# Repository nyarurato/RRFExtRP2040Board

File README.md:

# RP2040 CAN IO Expansion Board
This is a CAN-connected I/O expansion board for Duet3 (RepRapFirmware) using the RP2040 and MCP2518FD.
The circuit design was heavily inspired by the [Duet3 Mainboard 6HC](https://github.com/Duet3D/Duet3-Mainboard-6HC) and the [Fly-RRF-36](https://github.com/Mellow-3D/Fly-RRF-36).

---

# RP2040 CAN IO Expansion Board
RP2040 + MCP2518FD を使用した、Duet3 (RepRapFirmware) 向けの CAN 接続 IO 拡張基板です。
回路設計は[Duet3 Mainboard 6HC](https://github.com/Duet3D/Duet3-Mainboard-6HC)と[Fly-RRF-36](https://github.com/Mellow-3D/Fly-RRF-36)を大いに参考にしました。

## v0.1

## v0.2

# firmware
以下のRP2040 & MCP2517対応のDuet3Expansionフォークを使う  
https://github.com/gloomyandy/Duet3Expansion

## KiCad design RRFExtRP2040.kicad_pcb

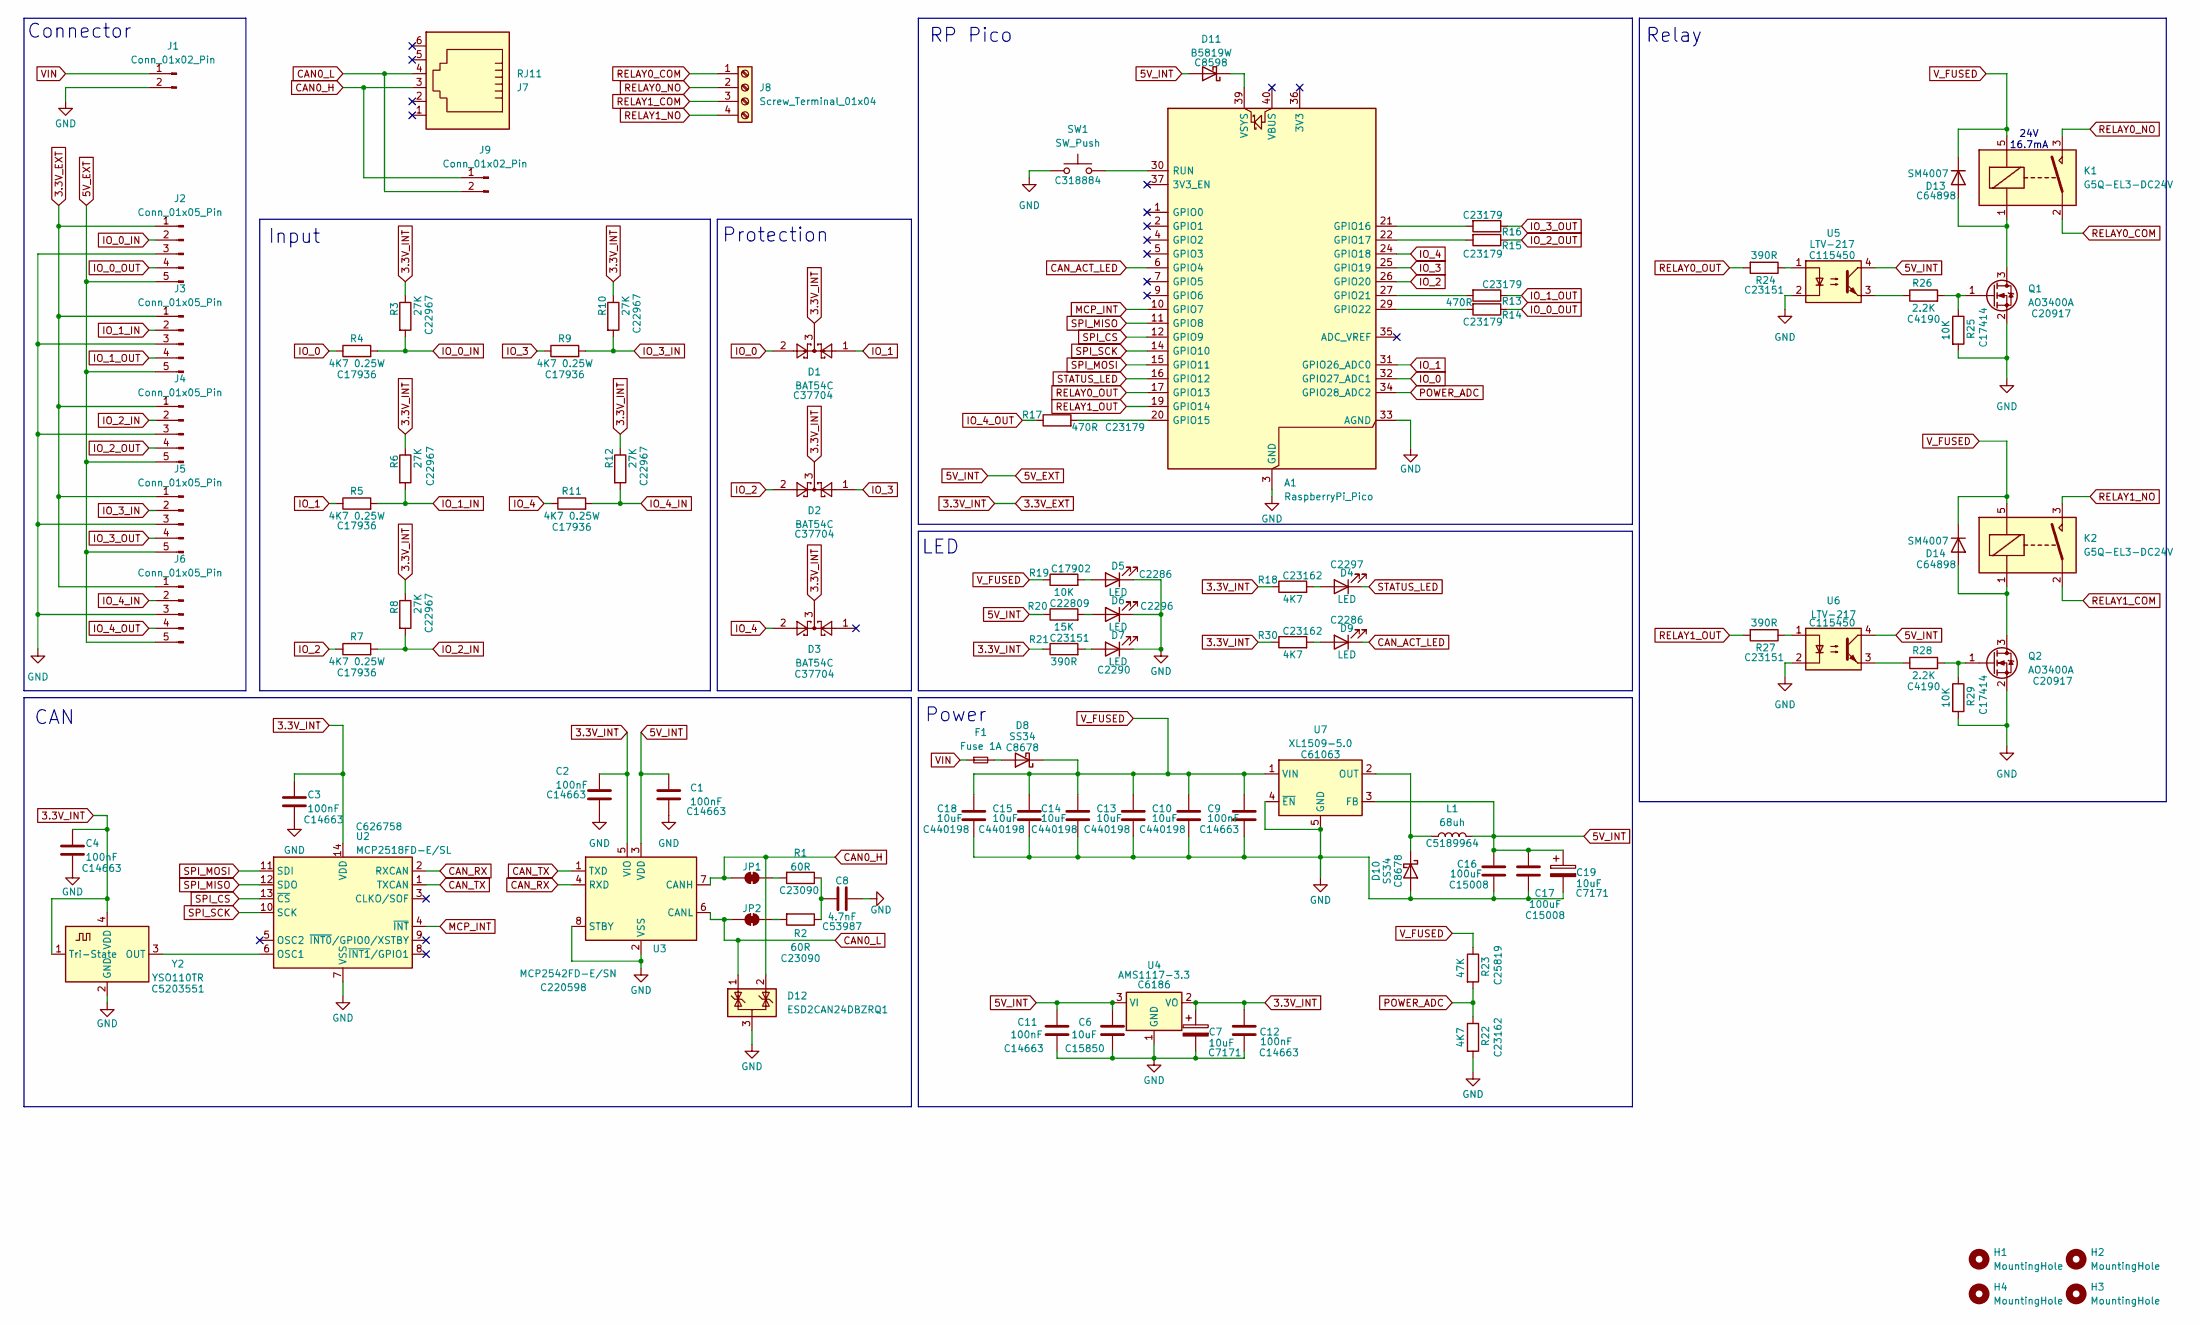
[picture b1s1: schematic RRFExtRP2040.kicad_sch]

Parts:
A1: RaspberryPi_Pico; RaspberryPi_Pico_Common_Unspecified
C1, C2, C3, C4, C9, C11, C12: 100nF; C_0603_1608Metric; LCSC PN C14663
C6: 10uF; C_0805_2012Metric; LCSC PN C15850
C7, C19: 10uF; CP_EIA-3216-18_Kemet-A; LCSC PN C7171
C8: 4.7nF; C_0603_1608Metric; LCSC PN C53987
C10, C13, C14, C15, C18: 10uF; C_0805_2012Metric; LCSC PN C440198
C16, C17: 100uF; C_1206_3216Metric; LCSC PN C15008
D1, D2, D3: BAT54C; SOT-23; LCSC PN C37704
D4: LED; LED_0805_2012Metric; LCSC PN C2297
D5, D9: LED; LED_0603_1608Metric; LCSC PN C2286
D6: LED; LED_0805_2012Metric; LCSC PN C2296
D7: LED; LED_0603_1608Metric; LCSC PN C2290
D8, D10: SS34; D_SMA; LCSC PN C8678
D11: B5819W; D_SOD-123; LCSC PN C8598
D12: ESD2CAN24DBZRQ1; SOT-23-3
D13, D14: SM4007; D_SOD-123F; LCSC PN C64898
F1: Fuse 1A; Fuse_1206_3216Metric
H1, H2, H3, H4: MountingHole; MountingHole_3.2mm_M3
J1: Conn_01x02_Pin; JST_VH_B2P-VH-B_1x02_P3.96mm_Vertical
J2, J3, J4, J5, J6: Conn_01x05_Pin; Molex_KK-254_AE-6410-05A_1x05_P2.54mm_Vertical
J7: RJ11; 615006138421
J8: Screw_Terminal_01x04; HB9500-9.5-4P
J9: Conn_01x02_Pin; Molex_KK-254_AE-6410-02A_1x02_P2.54mm_Vertical
JP1, JP2: SolderJumper_2_Bridged; SolderJumper-2_P1.3mm_Bridged_Pad1.0x1.5mm
K1, K2: G5Q-EL3-DC24V; Relay_SPST_Omron-G5Q-1A
L1: 68uh; IND-SMD_L7.2-W6.6_GPSR07X0; LCSC PN C5189964
Q1, Q2: AO3400A; SOT-23; LCSC PN C20917
R1, R2: 60R; R_0603_1608Metric; LCSC PN C23090
R3, R6, R8, R10, R12: 27K; R_0603_1608Metric; LCSC PN C22967
R4, R5, R7, R9, R11: 4K7 0.25W; R_1206_3216Metric; LCSC PN C17936
R13, R14, R15, R16, R17: 470R; R_0603_1608Metric; LCSC PN C23179
R18, R22, R30: 4K7; R_0603_1608Metric; LCSC PN C23162
R19: 10K; R_1206_3216Metric; LCSC PN C17902
R20: 15K; R_0603_1608Metric; LCSC PN C22809
R21, R24, R27: 390R; R_0603_1608Metric; LCSC PN C23151
R23: 47K; R_0603_1608Metric; LCSC PN C25819
R25, R29: 10K; R_0805_2012Metric; LCSC PN C17414
R26, R28: 2.2K; R_0603_1608Metric; LCSC PN C4190
SW1: SW_Push; SW_Push_1P1T_XKB_TS-1187A; LCSC PN C318884
U2: MCP2518FD-E/SL; SOIC-14_3.9x8.7mm_P1.27mm; LCSC PN C626758
U3: MCP2542FD-E/SN; SOIC-8_3.9x4.9mm_P1.27mm; LCSC PN C220598
U4: AMS1117-3.3; SOT-223-3_TabPin2; LCSC PN C6186
U5, U6: LTV-217; LTV217; LCSC PN C115450
U7: XL1509-5.0; SOIC-8_3.9x4.9mm_P1.27mm; LCSC PN C61063
Y2: YSO110TR; Crystal_SMD_3225-4Pin_3.2x2.5mm; LCSC PN C5203551

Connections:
3.3V_EXT: C2.1, C3.1, C4.1, C7.1, C12.2, D1.3, D2.3, D3.3, J2.1, J3.1, J4.1, J5.1, J6.1, R3.1, R6.1, R8.1, R10.1, R12.1, R18.1, R21.1, R30.1, U2.14 (VDD), U3.5 (VIO), U4.2 (VO), Y2.1 (Tri-State), Y2.4 (VDD)
5V_EXT: C1.1, C6.1, C11.1, C16.1, C17.1, C19.1, D11.2 (A), J2.5, J3.5, J4.5, J5.5, J6.5, L1.2, R20.1, U3.3 (VDD), U4.3 (VI), U5.4, U6.4, U7.3 (FB)
CAN0_H: D12.2 (K), J7.3, J9.1, JP1.1 (A), U3.7 (CANH)
CAN0_L: D12.1 (K), J7.4, J9.2, JP2.1 (A), U3.6 (CANL)
CAN_ACT_LED: A1.6 (GPIO4), D9.1 (K)
CAN_RX: U2.2 (RXCAN), U3.4 (RXD)
CAN_TX: U2.1 (TXCAN), U3.1 (TXD)
GND: A1.3 (GND), A1.8 (GND), A1.13 (GND), A1.18 (GND), A1.23 (GND), A1.28 (GND), A1.33 (AGND), A1.38 (GND), C1.2, C2.2, C3.2, C4.2, C6.2, C7.2, C8.2, C9.2, C10.2, C11.2, C12.1, C13.2, C14.2, C15.2, C16.2, C17.2, C18.2, C19.2, D5.1 (K), D6.1 (K), D7.1 (K), D10.2 (A), D12.3 (A), J1.2, J2.3, J3.3, J4.3, J5.3, J6.3, Q1.2 (S), Q2.2 (S), R22.2, R25.2, R29.2, SW1.1, U2.7 (VSS), U3.2 (VSS), U3.8 (STBY), U3.9 (VSS), U4.1 (GND), U5.2, U6.2, U7.4 (~EN), U7.5 (GND), U7.6 (GND), U7.7 (GND), U7.8 (GND), Y2.2 (GND)
IO_0: A1.32 (GPIO27_ADC1), D1.2, R4.1
IO_0_IN: J2.2, R3.2, R4.2
IO_0_OUT: J2.4, R14.1
IO_1: A1.31 (GPIO26_ADC0), D1.1, R5.1
IO_1_IN: J3.2, R5.2, R6.2
IO_1_OUT: J3.4, R13.1
IO_2: A1.26 (GPIO20), D2.2, R7.1
IO_2_IN: J4.2, R7.2, R8.2
IO_2_OUT: J4.4, R15.1
IO_3: A1.25 (GPIO19), D2.1, R9.1
IO_3_IN: J5.2, R9.2, R10.2
IO_3_OUT: J5.4, R16.1
IO_4: A1.24 (GPIO18), D3.2, R11.1
IO_4_IN: J6.2, R11.2, R12.2
IO_4_OUT: J6.4, R17.1
MCP_INT: A1.10 (GPIO7), U2.4 (~INT)
unnamed: A1.20 (GPIO15), R17.2
unnamed: A1.21 (GPIO16), R16.2
unnamed: A1.22 (GPIO17), R15.2
unnamed: A1.27 (GPIO21), R13.2
unnamed: A1.29 (GPIO22), R14.2
unnamed: A1.30 (RUN), SW1.2
unnamed: A1.39 (VSYS), D11.1 (K)
unnamed: C8.1, R1.1, R2.1
unnamed: D4.2 (A), R18.2
unnamed: D5.2 (A), R19.2
unnamed: D6.2 (A), R20.2
unnamed: D7.2 (A), R21.2
unnamed: D8.2 (A), F1.2
unnamed: D9.2 (A), R30.2
unnamed: D10.1 (K), L1.1, U7.2 (OUT)
unnamed: D13.2 (A), K1.1, Q1.3 (D)
unnamed: D14.2 (A), K2.1, Q2.3 (D)
unnamed: JP1.2 (B), R1.2
unnamed: JP2.2 (B), R2.2
unnamed: Q1.1 (G), R25.1, R26.2
unnamed: Q2.1 (G), R28.2, R29.1
unnamed: R24.1, U5.1
unnamed: R26.1, U5.3
unnamed: R27.1, U6.1
unnamed: R28.1, U6.3
unnamed: U2.6 (OSC1), Y2.3 (OUT)
POWER_ADC: A1.34 (GPIO28_ADC2), R22.1, R23.2
RELAY0_COM: J8.1, K1.2
RELAY0_NO: J8.2, K1.3
RELAY0_OUT: A1.17 (GPIO13), R24.2
RELAY1_COM: J8.3, K2.2
RELAY1_NO: J8.4, K2.3
RELAY1_OUT: A1.19 (GPIO14), R27.2
SPI_CS: A1.12 (GPIO9), U2.13 (~CS)
SPI_MISO: A1.11 (GPIO8), U2.12 (SDO)
SPI_MOSI: A1.15 (GPIO11), U2.11 (SDI)
SPI_SCK: A1.14 (GPIO10), U2.10 (SCK)
STATUS_LED: A1.16 (GPIO12), D4.1 (K)
VIN: F1.1, J1.1
V_FUSED: C9.1, C10.1, C13.1, C14.1, C15.1, C18.1, D8.1 (K), D13.1 (K), D14.1 (K), K1.5, K2.5, R19.1, R23.1, U7.1 (VIN)

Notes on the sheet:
CAN
RP Pico
24V 16.7mA
Connector
Protection
Relay
LED
Power
Input

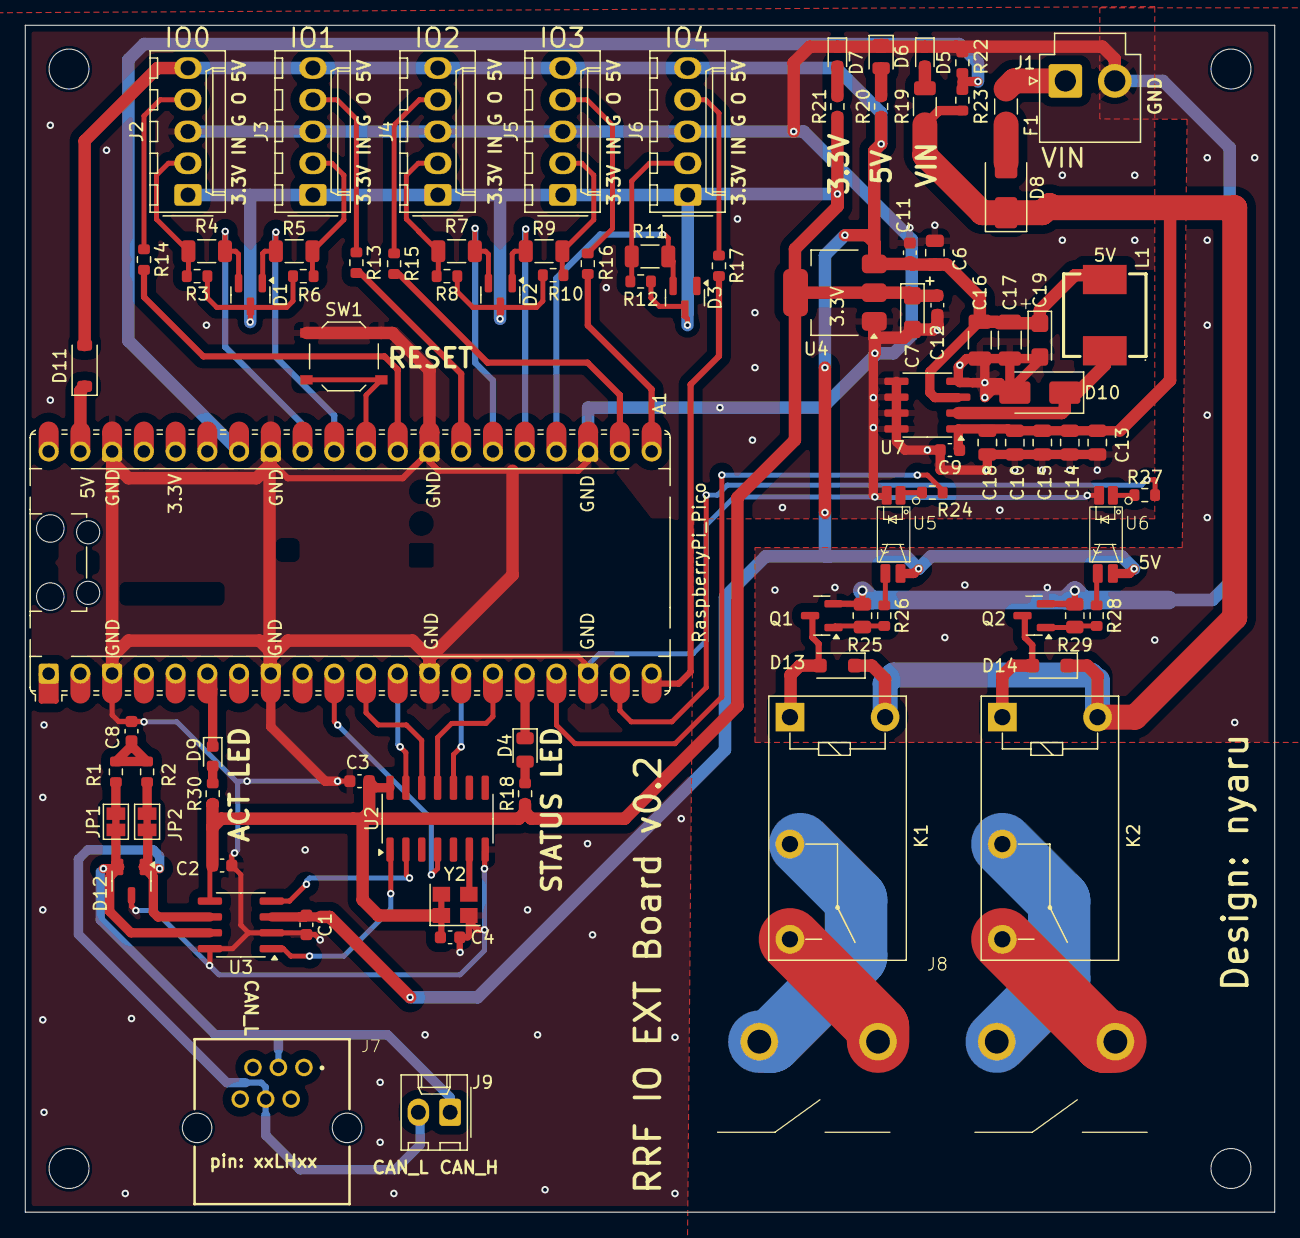
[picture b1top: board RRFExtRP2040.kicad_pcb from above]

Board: 2 copper layers, 100.0 x 95.0 mm, 92 parts (0 on the bottom side), 64 nets.

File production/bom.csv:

Designator,Footprint,Quantity,Value,LCSC Part #
A1,RaspberryPi_Pico_Common_Unspecified,1,RaspberryPi_Pico,
"C1, C11, C12, C2, C3, C4, C9",0603,7,100nF,C14663
"C10, C13, C14, C15, C18",0805,5,10uF,C440198
"C16, C17",1206,2,100uF,C15008
"C19, C7",CP_EIA-3216-18_Kemet-A,2,10uF,C7171
C6,0805,1,10uF,C15850
C8,0603,1,4.7nF,C53987
"D1, D2, D3",SOT-23,3,BAT54C,C37704
"D10, D8",D_SMA,2,SS34, C8678
D11,D_SOD-123,1,B5819W,C8598
D12,SOT-23-3,1,ESD2CAN24DBZRQ1,
"D13, D14",D_SOD-123F,2,SM4007,C64898
D4,0805,1,LED,C2297
"D5, D9",0603,2,LED,C2286
D6,0805,1,LED,C2296
D7,0603,1,LED,C2290
F1,1206,1,Fuse 1A,
J1,JST_VH_B2P-VH-B_1x02_P3.96mm_Vertical,1,Conn_01x02_Pin,
"J2, J3, J4, J5, J6",Molex_KK-254_AE-6410-05A_1x05_P2.54mm_Vertical,5,Conn_01x05_Pin,
J7,615006138421,1,RJ11,
J8,HB9500-9.5-4P,1,Screw_Terminal_01x04,
J9,Molex_KK-254_AE-6410-02A_1x02_P2.54mm_Vertical,1,Conn_01x02_Pin,
"K1, K2",Relay_SPST_Omron-G5Q-1A,2,G5Q-EL3-DC24V,
L1,IND-SMD_L7.2-W6.6_GPSR07X0,1,68uh,C5189964
"Q1, Q2",SOT-23,2,AO3400A,C20917 
"R1, R2",0603,2,60R,C23090
"R10, R12, R3, R6, R8",0603,5,27K,C22967
"R11, R4, R5, R7, R9",1206,5,4K7 0.25W,C17936
"R13, R14, R15, R16, R17",0603,5,470R,C23179
"R18, R22, R30",0603,3,4K7,C23162
R19,1206,1,10K,C17902
R20,0603,1,15K,C22809
"R21, R24, R27",0603,3,390R,C23151
R23,0603,1,47K,C25819
"R25, R29",0805,2,10K,C17414
"R26, R28",0603,2,2.2K,C4190
SW1,SW_Push_1P1T_XKB_TS-1187A,1,SW_Push,C318884
U2,SOIC-14_3.9x8.7mm_P1.27mm,1,MCP2518FD-E/SL,C626758
U3,SOIC-8_3.9x4.9mm_P1.27mm,1,MCP2542FD-E/SN,C220598
U4,SOT-223-3_TabPin2,1,AMS1117-3.3,C6186 
"U5, U6",LTV217,2,LTV-217, C115450
U7,SOIC-8_3.9x4.9mm_P1.27mm,1,XL1509-5.0, C61063
Y2,Crystal_SMD_3225-4Pin_3.2x2.5mm,1,YSO110TR,C5203551

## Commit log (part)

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2026-02-25 v0.1
2026-03-30 fix sch
2026-03-30 update docs
